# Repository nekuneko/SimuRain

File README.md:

## Instructions (Work in progress...)

The system currently works following the flow:

* The program is loaded into the ROM of the card and gets activated when receives electric power and the serial port is opened.

* When running, the program writes every 2 second the data received from the different sensors. So running the Arduino IDE showing the serial port is recommended. This information is needed firstly to calibrate the instruments of the experiment.

* Software records day-time, Ph and temperature every two seconds.

* The output file is "datalog.txt", but it can be modified in the source code. It includes Windows CRLF, in UTF-8 format.

* Every time new data is recorded in the microSD card, the modification date of the file in the operating system is modified.

* New data is appended at the end of the file. If user needs data separated into different files, (s)he has to do it manually.

Troubleshooting:

* In case of problems when writing in the card, formatting the SD card with the "SD Card Formatter" software is recommended: https://www.sdcard.org/downloads/formatter_4/index.html

* In case the time is not synchronized (or too early/delayed) it can be re-adjusted: disconnect electric power, take the batteries off using a screwdriver and, after 10 seconds, connect it again and load the program anew. The system, when the serial port will be opened, will detect that there is no actual time and will use the compilation time of the program as current time.

## Instrucciones provisionales (Work in progress...)

El programa actualmente funciona de la siguiente manera:

* El programa se carga en la ROM de la tarjeta y se activa cuando recibe alimentación y se abre el puerto serial. En el puerto serial se van mostrando las lecturas y otra información, por lo que hace falta tener e Arduino IDE y mostrar el puerto serial. Esta información puede servir para la calibración del experimento.

* El software registra dia-hora, Ph y temperatura (no caudal), espera hasta que terminen de pasar 2 segundos y vuelve a hacerlo.

* El nombre del fichero de salida es "datalog.txt", su puede cambiar al inicio del programa. El fichero tiene final de línea Windows CRLF, codificado en UTF-8.

* Cuando se escribe en la tarjeta microSD, se guarda la fecha de modificación de la última vez que fue escrita.

* El contenido se añade al final del fichero. Si se desean separar los datos hay que hacerlo a mano desde el ordenador.

En caso de problemas:

* Si hay problemas de escritura se debe probar a formatear la tarjeta microSD con el software "SD Card Formatter": https://www.sdcard.org/downloads/formatter_4/index.html

* Si se pierde la hora (o el reloj atrasa/adelanta más de lo deseado) se puede ajustar la hora. Para hacerlo se desconecta todo de la alimentación eléctrica, se saca la pila con un destornillador, se esperan 10 segundos, se vuelve a conectar y se vuelve a subir el programa. El sistema, cuando se abra el puerto serial, detectará que no tiene horay cogerá la hora de la última compilación del programa como hora actual para desde ahí empezará a contar.

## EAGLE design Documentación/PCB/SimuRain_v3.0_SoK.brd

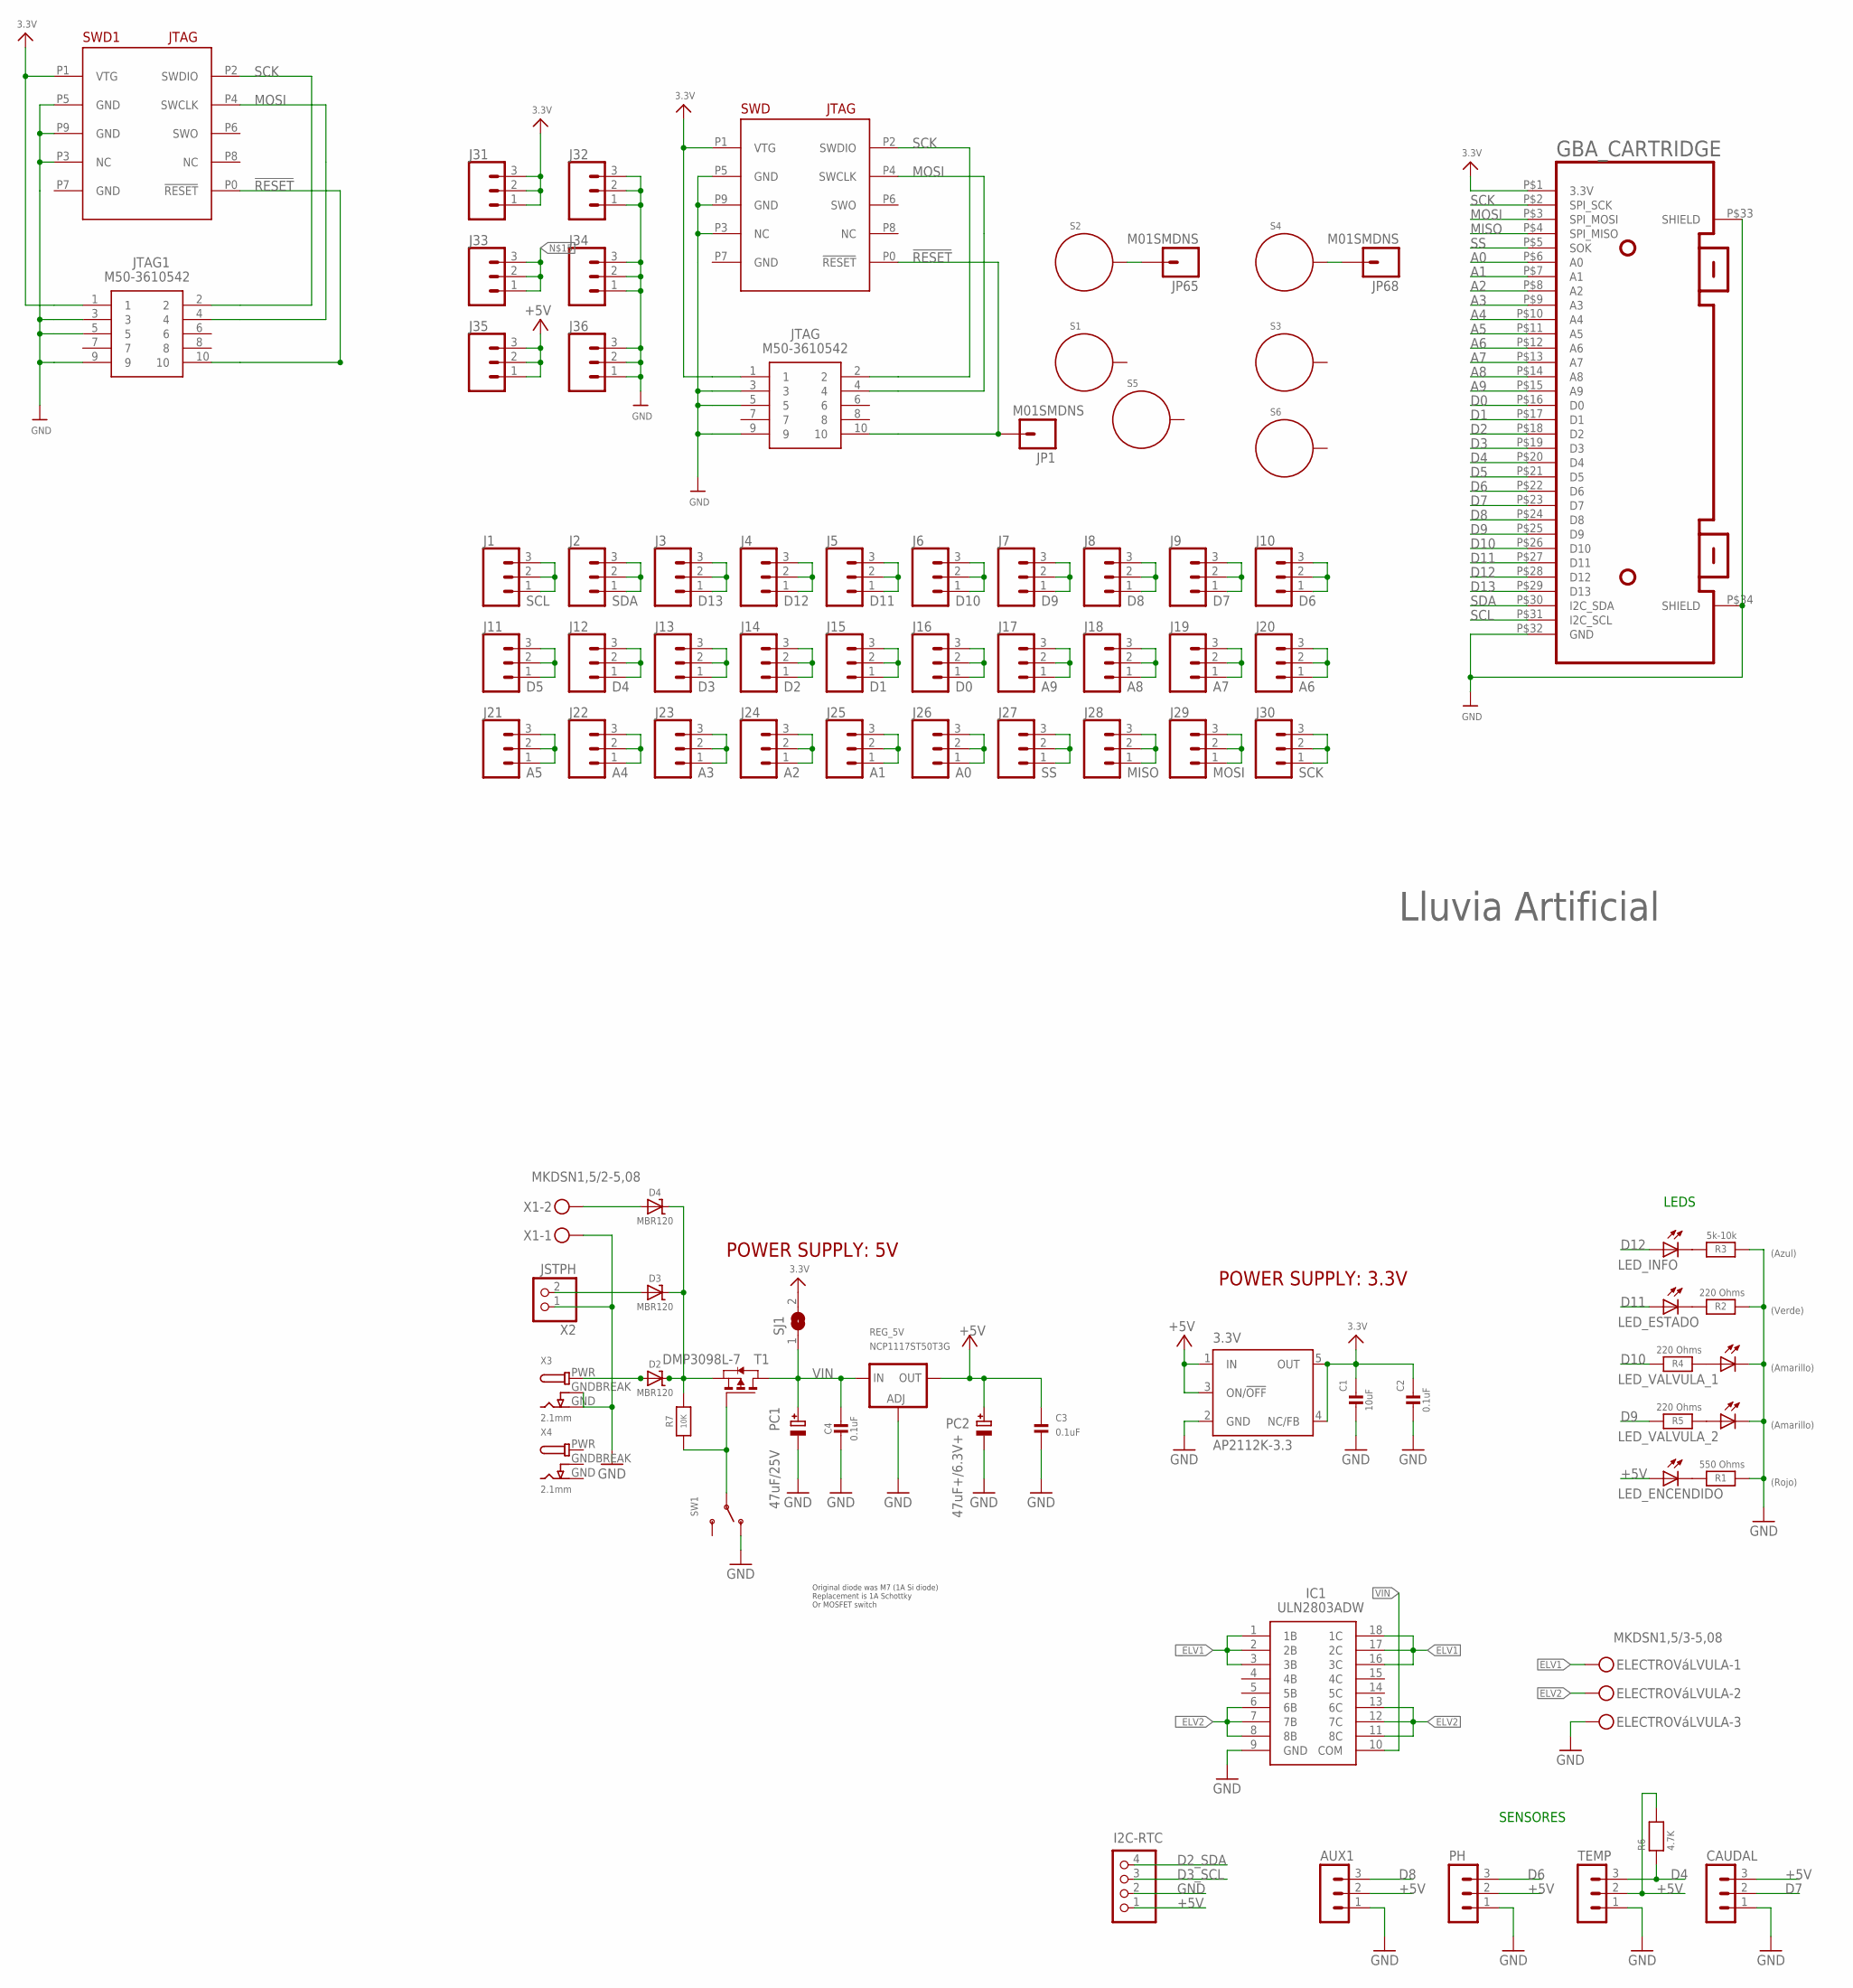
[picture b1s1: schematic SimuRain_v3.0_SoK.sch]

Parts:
3.3V: AP2112K-3.3; SOT23-DBV
AUX1: MA03-1
C1: 10uF; _0603
C2, C3, C4: 0.1uF; _0603
CAUDAL: MA03-1
D2, D3, D4: MBR120; SOD-123
ELECTROVáLVULA: MKDSN1,5/3-5,08
GBA_CARTRIDGE: GBA_CARTRIDGEGBA_CARTRIDGE2; GBA_CARTRIDGE2
I2C-RTC: HEADER-1X4; 1X04_OVAL
IC1: ULN2803ADW; SOIC127P1030X265-18N
J1, J2, J3, J4, J5, J6, J7, J8, J9, J10, J11, J12, J13, J14, J15, J16, J17, J18, J19, J20, J21, J22, J23, J24, J25, J26, J27, J28, J29, J30, J31, J32, J33, J34, J35, J36: CONN_031X03_NO_SILK; 1X03_NO_SILK
JP1, JP65, JP68: M01SMDNS; 1X01NS
JTAG, JTAG1: M50-3610542; M503610542
LED_ENCENDIDO: LED5MM
LED_ESTADO: LED5MM
LED_INFO: LED5MM
LED_VALVULA_1, LED_VALVULA_2: LED5MM
PC1: 47uF/25V; PANASONIC_D
PC2: 47uF+/6.3V+; PANASONIC_D
PH: MA03-1
R1: 550 Ohms; _0805
R2, R4, R5: 220 Ohms; _0805
R3: 5k-10k; _0805
R6: 4.7K; _0805
R7: 10K; _0805
REG_5V: NCP1117ST50T3G; SOT223-R
S1, S2, S3, S4, S5, S6: STANDOFF_ELECTRICAL; STANDOFF-ELECTRICAL
SJ1: SOLDERJUMPERREFLOW_NOPASTE; SOLDERJUMPER_REFLOW_NOPASTE
SW1: SWITCH_SPDT; SPDT_SMT_SSSS811101
SWD, SWD1: JTAGICE3-CONNECTOR50MIL-THT; JTAGICE3-50MIL
T1: DMP3098L-7; SOT-23
TEMP: MA03-1
X1: MKDSN1,5/2-5,08
X2: JSTPH; JSTPH2
X3, X4: 2.1mm; DCJACK_2MM_PTH

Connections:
3.3V: 3.3V.4 (NC/FB), 3.3V.5 (OUT), C1.1, C2.1, GBA_CARTRIDGE.P$1 (3.3V), J31.1, J31.2, J31.3, JTAG.1, JTAG1.1, SJ1.2, SWD.P1 (VTG), SWD1.P1 (VTG)
!RESET: JP1.1, JTAG.10, JTAG1.10, SWD.P0 (!RESET), SWD1.P0 (!RESET)
+5V: 3.3V.1 (IN), 3.3V.3 (ON/!OFF), AUX1.2, C3.1, CAUDAL.3, I2C-RTC.1, J35.1, J35.2, J35.3, LED_ENCENDIDO.A, PC2.+, PH.2, R6.2, REG_5V.2 (OUT), REG_5V.4 (OUT), TEMP.2
A0: GBA_CARTRIDGE.P$6 (A0), J26.1, J26.2, J26.3
A1: GBA_CARTRIDGE.P$7 (A1), J25.1, J25.2, J25.3
A2: GBA_CARTRIDGE.P$8 (A2), J24.1, J24.2, J24.3
A3: GBA_CARTRIDGE.P$9 (A3), J23.1, J23.2, J23.3
A4: GBA_CARTRIDGE.P$10 (A4), J22.1, J22.2, J22.3
A5: GBA_CARTRIDGE.P$11 (A5), J21.1, J21.2, J21.3
A6: GBA_CARTRIDGE.P$12 (A6), J20.1, J20.2, J20.3
A7: GBA_CARTRIDGE.P$13 (A7), J19.1, J19.2, J19.3
A8: GBA_CARTRIDGE.P$14 (A8), J18.1, J18.2, J18.3
A9: GBA_CARTRIDGE.P$15 (A9), J17.1, J17.2, J17.3
D0: GBA_CARTRIDGE.P$16 (D0), J16.1, J16.2, J16.3
D1: GBA_CARTRIDGE.P$17 (D1), J15.1, J15.2, J15.3
D2: GBA_CARTRIDGE.P$18 (D2), J14.1, J14.2, J14.3
D2_SDA: I2C-RTC.4
D3: GBA_CARTRIDGE.P$19 (D3), J13.1, J13.2, J13.3
D3_SCL: I2C-RTC.3
D4: GBA_CARTRIDGE.P$20 (D4), J12.1, J12.2, J12.3, R6.1, TEMP.3
D5: GBA_CARTRIDGE.P$21 (D5), J11.1, J11.2, J11.3
D6: GBA_CARTRIDGE.P$22 (D6), J10.1, J10.2, J10.3, PH.3
D7: CAUDAL.2, GBA_CARTRIDGE.P$23 (D7), J9.1, J9.2, J9.3
D8: AUX1.3, GBA_CARTRIDGE.P$24 (D8), J8.1, J8.2, J8.3
D9: GBA_CARTRIDGE.P$25 (D9), J7.1, J7.2, J7.3, R5.1
D10: GBA_CARTRIDGE.P$26 (D10), J6.1, J6.2, J6.3, R4.1
D11: GBA_CARTRIDGE.P$27 (D11), J5.1, J5.2, J5.3, LED_ESTADO.A
D12: GBA_CARTRIDGE.P$28 (D12), J4.1, J4.2, J4.3, LED_INFO.A
D13: GBA_CARTRIDGE.P$29 (D13), J3.1, J3.2, J3.3
ELV1: ELECTROVáLVULA.1, IC1.16 (3C), IC1.17 (2C), IC1.18 (1C)
ELV2: ELECTROVáLVULA.2, IC1.11 (8C), IC1.12 (7C), IC1.13 (6C)
GND: 3.3V.2 (GND), AUX1.1, C1.2, C2.2, C3.2, C4.2, CAUDAL.1, ELECTROVáLVULA.3, GBA_CARTRIDGE.P$32 (GND), GBA_CARTRIDGE.P$33 (SHIELD), GBA_CARTRIDGE.P$34 (SHIELD), I2C-RTC.2, IC1.9 (GND), J32.1, J32.2, J32.3, J34.1, J34.2, J34.3, J36.1, J36.2, J36.3, JTAG.3, JTAG.5, JTAG.9, JTAG1.3, JTAG1.5, JTAG1.9, LED_VALVULA_1.K (C), LED_VALVULA_2.K (C), PC1.-, PC2.-, PH.1, R1.2, R2.2, R3.2, REG_5V.1 (ADJ), SW1.A (O), SWD.P3 (NC), SWD.P5 (GND), SWD.P9 (GND), SWD1.P3 (NC), SWD1.P5 (GND), SWD1.P9 (GND), TEMP.1, X1.1, X2.1, X3.GND, X3.GNDBREAK, X4.GND
GNDBREAK: X4.GNDBREAK
MISO: GBA_CARTRIDGE.P$4 (SPI_MISO), J28.1, J28.2, J28.3
MOSI: GBA_CARTRIDGE.P$3 (SPI_MOSI), J29.1, J29.2, J29.3, JTAG.4, JTAG1.4, SWD.P4 (SWCLK), SWD1.P4 (SWCLK)
unnamed: D4.A, X1.2
unnamed: D3.A, X2.2
unnamed: LED_ENCENDIDO.K (C), R1.1
unnamed: LED_ESTADO.K (C), R2.1
unnamed: LED_INFO.K (C), R3.1
unnamed: LED_VALVULA_2.A, R5.2
unnamed: LED_VALVULA_1.A, R4.2
unnamed: D2.C, D3.C, D4.C, J33.1, J33.2, J33.3, R7.2, T1.2 (S)
unnamed: JP65.1, S2.P1
unnamed: JP68.1, S4.P1
PWR: X4.PWR
PWRIN: D2.A, X3.PWR
PWR_SWITCH: R7.1, SW1.B, T1.3 (G)
SCK: GBA_CARTRIDGE.P$2 (SPI_SCK), J30.1, J30.2, J30.3, JTAG.2, JTAG1.2, SWD.P2 (SWDIO), SWD1.P2 (SWDIO)
SCL: GBA_CARTRIDGE.P$31 (I2C_SCL), J1.1, J1.2, J1.3
SDA: GBA_CARTRIDGE.P$30 (I2C_SDA), J2.1, J2.2, J2.3
SS: GBA_CARTRIDGE.P$5 (SOK), J27.1, J27.2, J27.3
VIN: C4.1, IC1.10 (COM), PC1.+, REG_5V.3 (IN), SJ1.1, T1.1 (D)
_ELV1: IC1.1 (1B), IC1.2 (2B), IC1.3 (3B)
_ELV2: IC1.6 (6B), IC1.7 (7B), IC1.8 (8B)

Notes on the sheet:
Lluvia Artificial
Original diode was M7 (1A Si diode) Replacement is 1A Schottky Or MOSFET switch
POWER SUPPLY: 5V
POWER SUPPLY: 3.3V
SENSORES
LEDS
(Azul)
(Verde)
(Amarillo)
(Rojo)

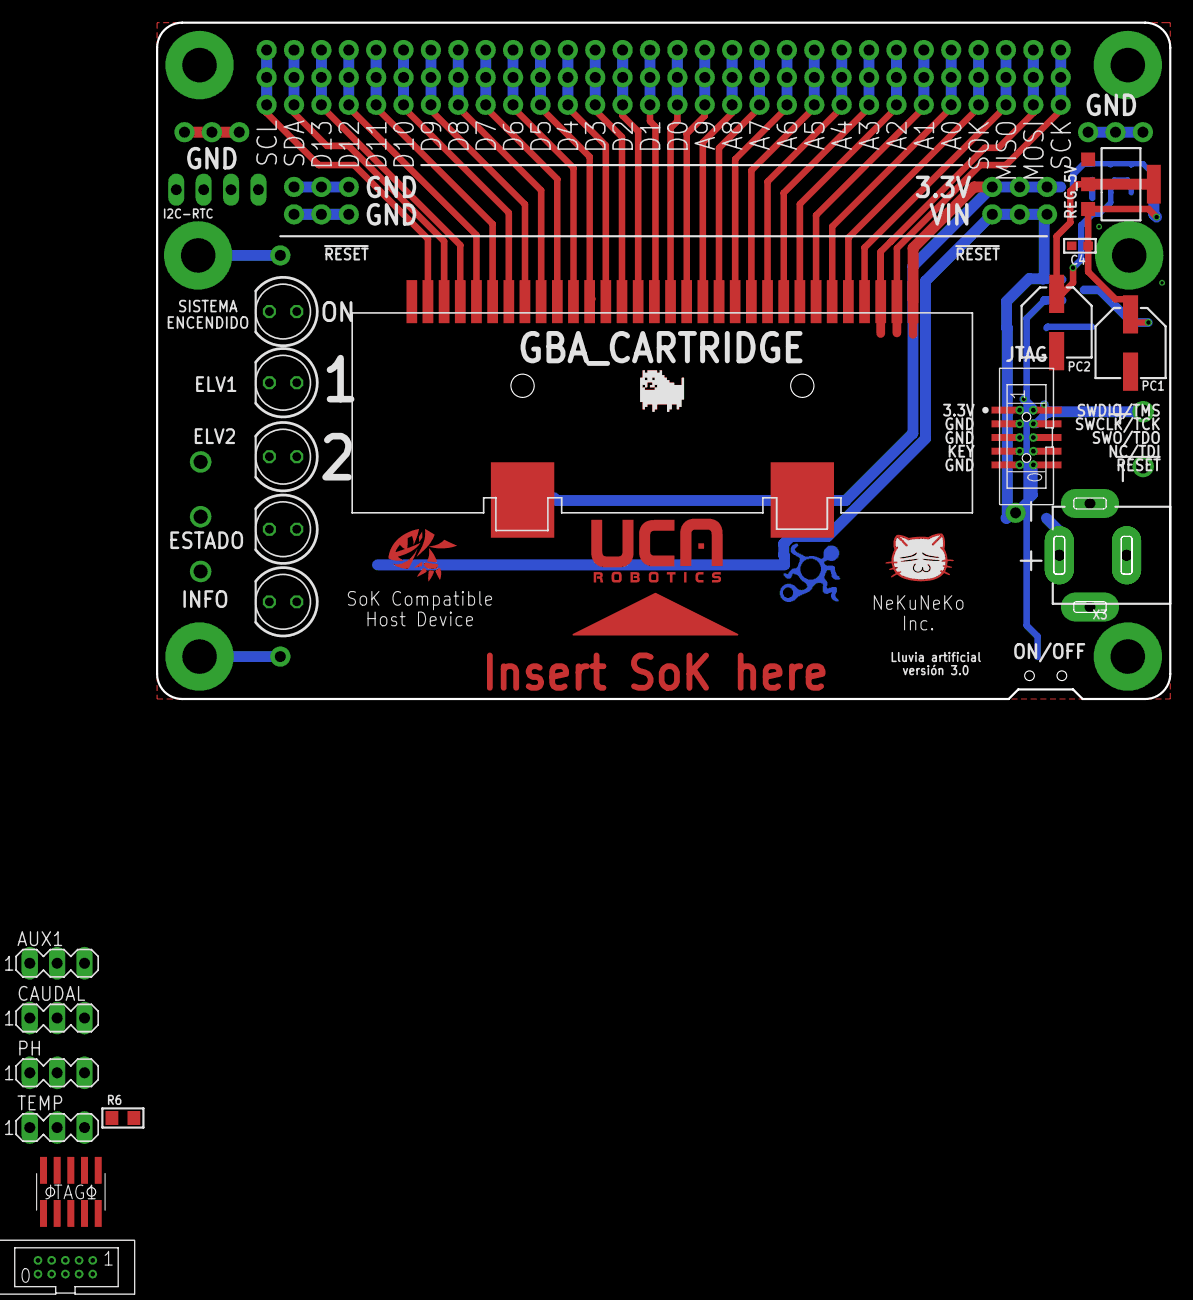
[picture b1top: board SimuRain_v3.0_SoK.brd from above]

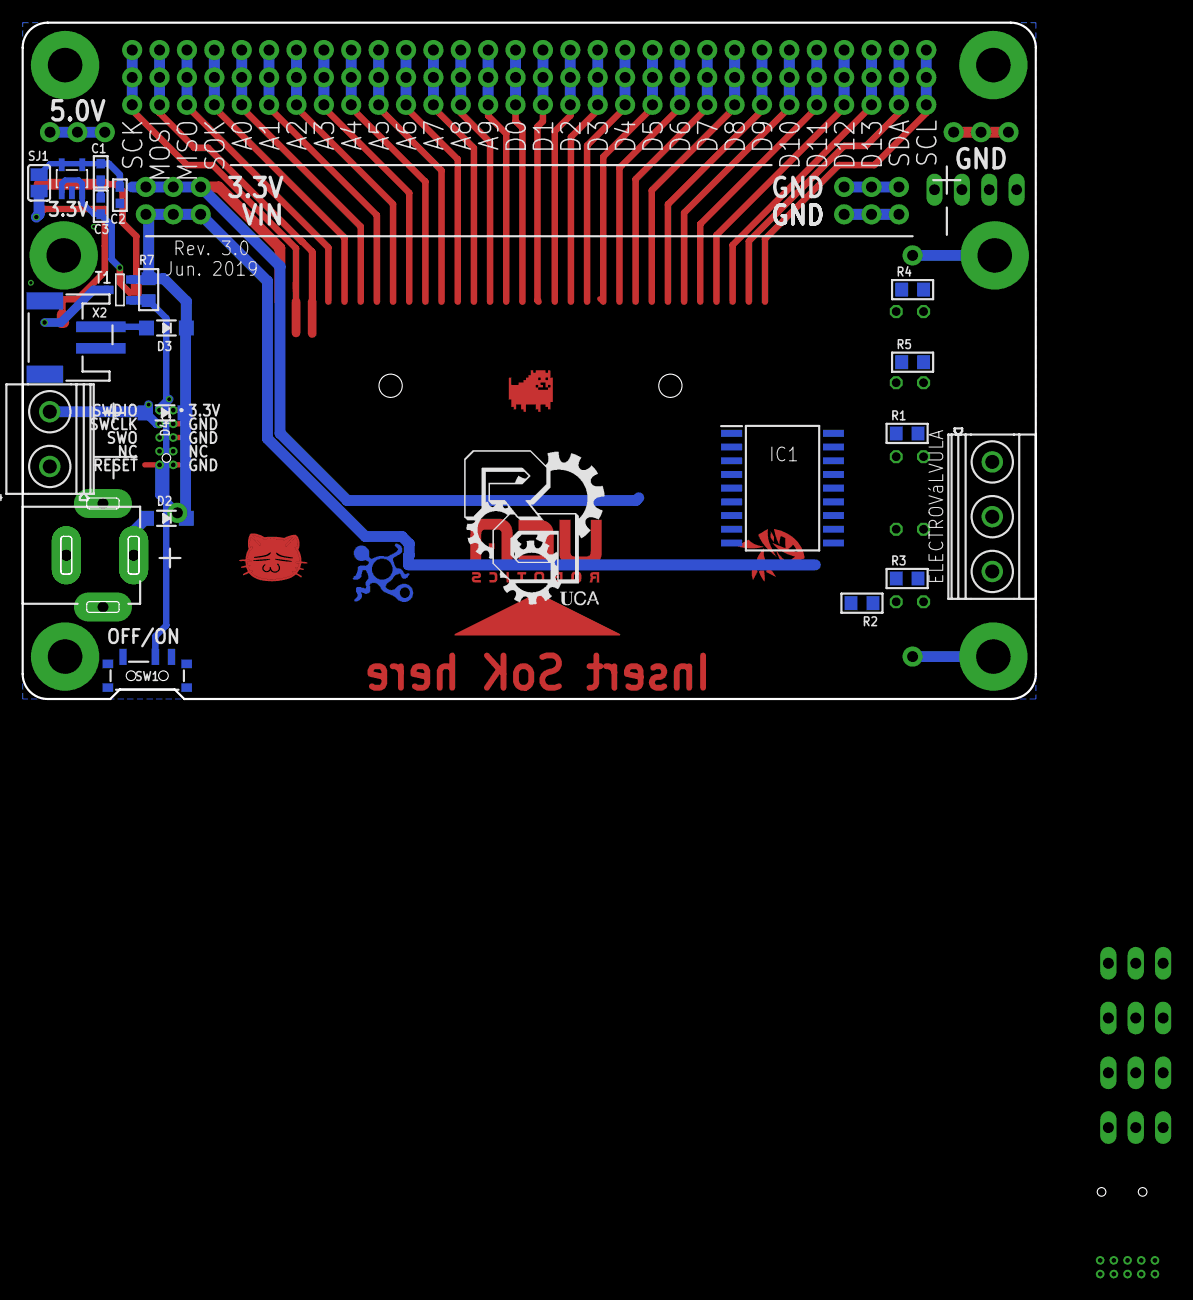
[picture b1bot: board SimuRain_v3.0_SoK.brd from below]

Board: 2 copper layers, 94.0 x 62.7 mm, 94 parts (57 on the bottom side), 51 nets.

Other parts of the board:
U$1: NEKO_6_5_BORDE_TPLACE
U$2: DOG
U$3: SOK_FINISH
U$9: GIRA
U$10: UCAROBOTICS
U$15: BUGS_6
U$50: TRIANGLE

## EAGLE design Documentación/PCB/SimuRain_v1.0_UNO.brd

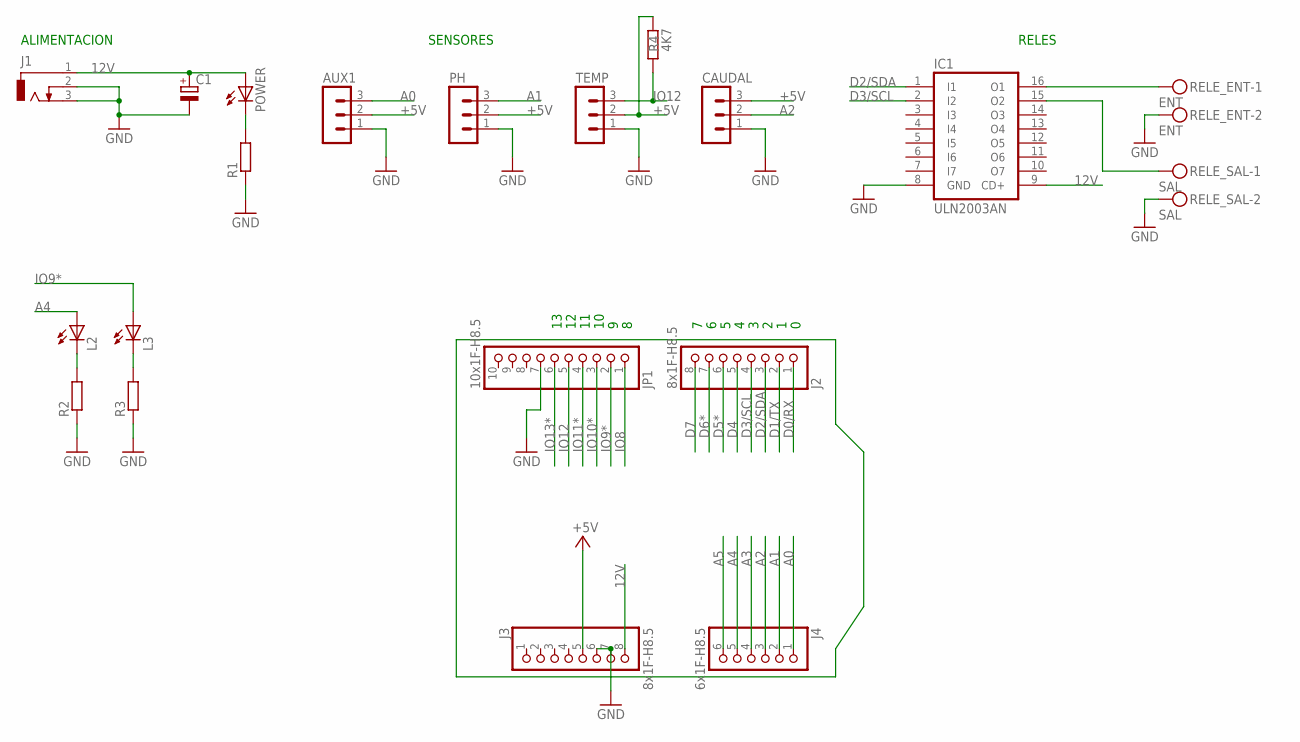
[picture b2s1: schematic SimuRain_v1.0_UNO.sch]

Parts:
AUX1: MA03-1
C1: CPOL-EUE5-6; E5-6
CAUDAL: MA03-1
IC1: ULN2003AN; DIL16
J1: DCJ0303
J2, J3: 8x1F-H8.5; 1X08
J4: 6x1F-H8.5; 1X06
JP1: 10x1F-H8.5; 1X10
L2, L3: LED5MM
PH: MA03-1
POWER: LED5MM
R1, R2, R3: R-EU_0204/5; 0204/5
R4: 4K7; 0204/5
RELE_ENT: ENT; MKDSN1,5/2-5,08
RELE_SAL: SAL; MKDSN1,5/2-5,08
TEMP: MA03-1

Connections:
12V: C1.+, IC1.9 (CD+), J1.1, J3.8, POWER.A
+5V: AUX1.2, CAUDAL.3, J3.5, PH.2, R4.2, TEMP.2
A0: AUX1.3, J4.1
A1: J4.2, PH.3
A2: CAUDAL.2, J4.3
A3: J4.4
A4: J4.5, L2.A
A5: J4.6
D0/RX: J2.1
D1/TX: J2.2
D2/SDA: IC1.1 (I1), J2.3
D3/SCL: IC1.2 (I2), J2.4
D4: J2.5
D5*: J2.6
D6*: J2.7
D7: J2.8
GND: AUX1.1, C1.-, CAUDAL.1, IC1.8 (GND), J1.2, J1.3, J3.6, J3.7, JP1.7, PH.1, R1.1, R2.1, R3.1, RELE_ENT.2, RELE_SAL.2, TEMP.1
IO8: JP1.1
IO9*: JP1.2, L3.A
IO10*: JP1.3
IO11*: JP1.4
IO12: JP1.5, R4.1, TEMP.3
IO13*: JP1.6
unnamed: IC1.16 (O1), RELE_ENT.1
unnamed: IC1.15 (O2), RELE_SAL.1
unnamed: L2.K (C), R2.2
unnamed: L3.K (C), R3.2
unnamed: POWER.K (C), R1.2

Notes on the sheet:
ALIMENTACION
SENSORES
RELES

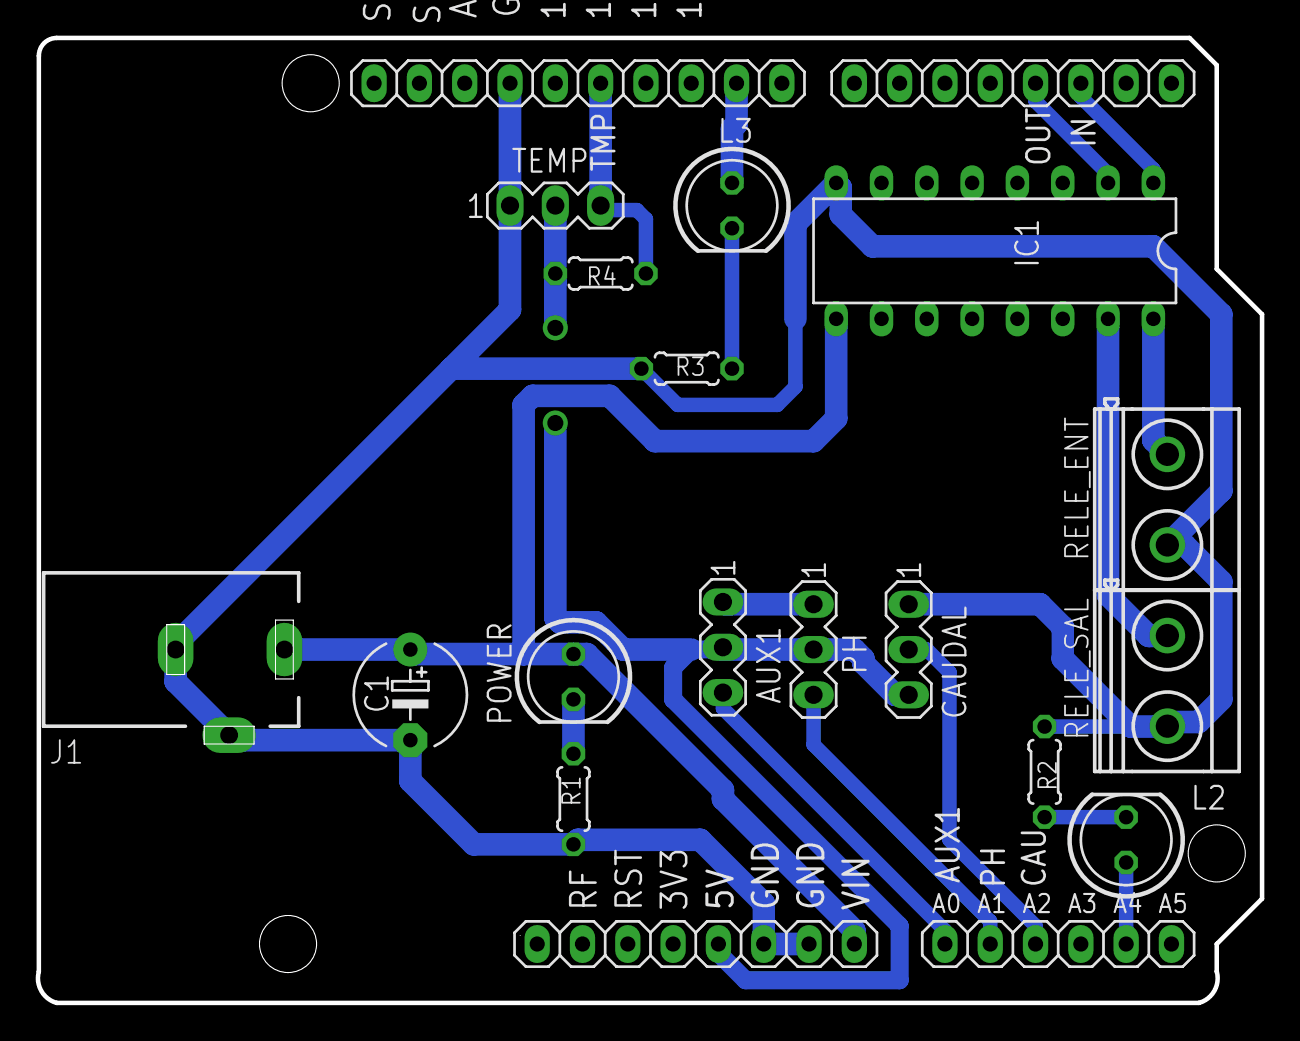
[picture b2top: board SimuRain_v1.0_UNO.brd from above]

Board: 2 copper layers, 68.6 x 54.1 mm, 20 parts (0 on the bottom side), 16 nets.

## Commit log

2019-07-22 Importación desde Bitbucket

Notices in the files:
parts and their libraries:
SparkFun-Electromechanical: Licensing: CC v3.0 Share-Alike You are welcome to use this library for commercial purposes.
microbuilder: This work is placed in the public domain, and may be freely used for commercial and non-commercial work with the following conditions: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
